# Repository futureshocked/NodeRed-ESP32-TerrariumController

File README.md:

# Node-RED and ESP32: make a terrarium controller

Flows, ESP32 sketches and the KiCad project for the Tech Explorations course [Node-RED and ESP32: make a terrarium controller](https://app.techexplorations.com/courses/node-red-esp32-make-a-terrarium-controller/).

## Project status (October 2026)

The course was recorded in 2020 with Node-RED 1.1 and Node.js 12. The project still works on current software: flow v6 was tested unchanged on Node-RED 5.0.8 with Node.js 22 and 26. The Node-RED editor, the install process and some third-party services have changed since recording.

- **Following the course now?** Read [UPDATE-2026.md](UPDATE-2026.md) first. It covers installing Node-RED 5, the new editor, the deprecated dashboard, Mosquitto 2, and services that have changed (IFTTT webhooks now need a paid plan).
- **What comes next:** [COURSE-UPDATE-PLAN.md](COURSE-UPDATE-PLAN.md) describes the planned revision, including replacing the DHT22, Google Sheets and IFTTT with open-source alternatives.

## What the project does

An ESP32 in the terrarium reads soil moisture, air temperature and humidity, and the voltages of the pump motor supply and its own battery. It publishes these readings over MQTT to a Mosquitto broker on a Raspberry Pi. Node-RED on the Pi subscribes to the readings, shows them on a web dashboard, decides when the soil is dry enough to run the water pump, and sends the pump command back to the ESP32 over MQTT. Later versions add a dashboard control for the moisture threshold, data logging and a low-battery alert.

## Repository contents

### Terrarium controller flows

Each version builds on the previous one, following the course.

| File | Adds |
|---|---|
| `TerrariumController-Flow-v1.json` | Soil moisture gauge and pump control over MQTT |
| `TerrariumController-Flow-v2.json` | Motor and MCU battery voltage gauges |
| `TerrariumController-Flow-v3.json` | Logging to Google Sheets |
| `TerrariumController-Flow-v4.json` | Dashboard control for the soil moisture threshold |
| `TerrariumController-Flow-v5.json` | Air temperature and humidity gauges |
| `TerrariumController-Flow-v6.json` | Low MCU battery alert through IFTTT |

### ESP32 sketches

`ESP32-TerariumControl-v1` to `v6` are the matching sketches. Each folder has an `esp32_secrets.h` file; fill in your Wi-Fi and MQTT broker details before uploading. The sketches need these libraries: EspMQTTClient, TaskScheduler (from v4) and DHTesp (v6).

### Example flows

Smaller flows used in the early lectures to introduce Node-RED concepts:

- Core nodes: `Inject-Function-flow.json`, `Switch-flow.json`, `Global-Variables-context-examples-flows.json`
- Dashboard widgets: `Basic-dashboard-example-flow.json`, `Dashboard-example-flow.json`, `Button-flow.json`, `Dropdown-template-flow.json`, `Form-flow.json`, `gauge-flow.json`
- Messaging and web services: `mqtt-example-flows.json`, `websockets-flow.json`, `dweetio-flow.json`, `ifttt-flow.json`
- DHT22 sensor on the Raspberry Pi: `DHT22-ex1-flow.json`, `DHT22-ex2-flow.json`, `DHT22-complete-example-flow.json`

### Hardware

`KiCad Terrarium Controller project/` contains the schematic and PCB for the controller board (KiCad 9 format), a PDF of the original schematic, and Gerber files. The LED orientation in the schematic was corrected in November 2025.

## Requirements

- Raspberry Pi 3, 4 or 5 with a 64-bit OS (or any computer that runs Node-RED)
- Node-RED 5 on Node.js 24 LTS (Node.js 22.9 or later is required; 26 also works)
- Mosquitto MQTT broker
- `node-red-dashboard` installed from the Node-RED Palette Manager
- ESP32 development board and the components listed in the course

## Importing a flow

In the Node-RED editor, open the main menu, choose Import, and paste the contents of a flow file or select the file. Install `node-red-dashboard` first, otherwise the dashboard nodes appear as "unknown". After importing, open the MQTT broker node and set your broker address, username and password.

## Help

Questions about the course go in the course Q&A. When reporting a problem, include the lecture number, your Node-RED and Node.js versions, and the exact error message.

## Licence

MIT, see [LICENSE](LICENSE).

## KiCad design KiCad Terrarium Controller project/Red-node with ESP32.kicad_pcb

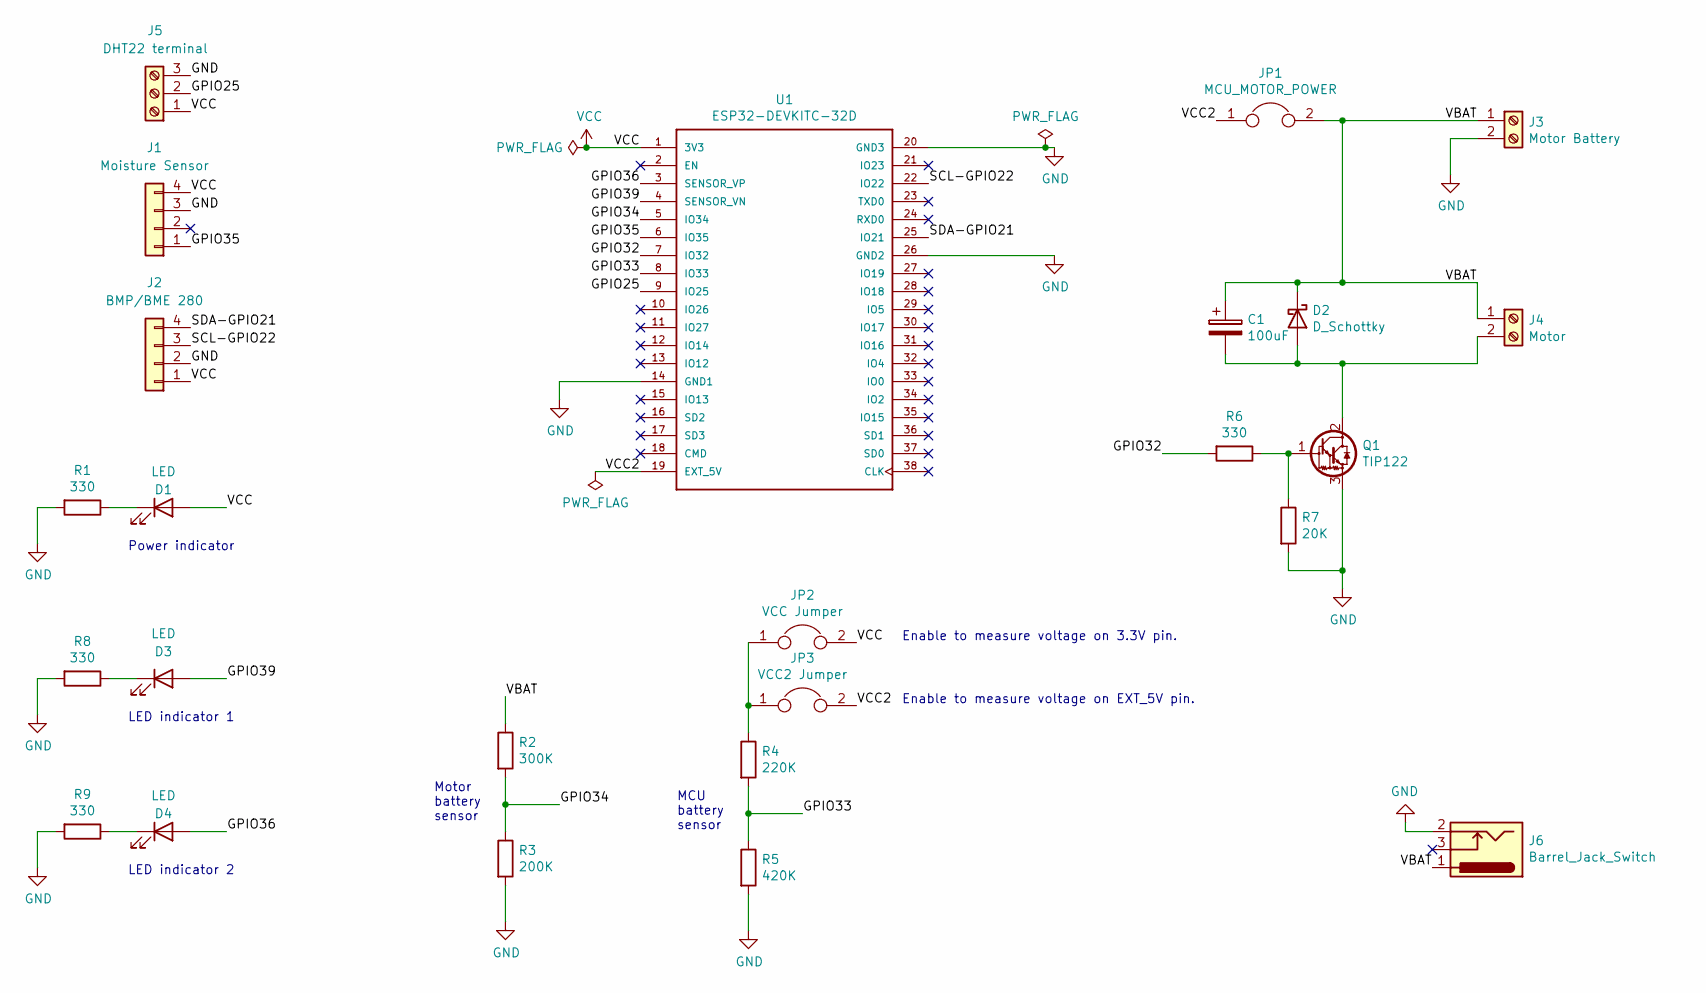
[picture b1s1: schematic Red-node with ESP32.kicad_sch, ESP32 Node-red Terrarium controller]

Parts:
C1: 100uF; CP_Radial_D8.0mm_P3.80mm
D1, D3, D4: LED; LED_D5.0mm
D2: D_Schottky; D_DO-41_SOD81_P7.62mm_Horizontal
J1: Moisture Sensor; PinHeader_1x04_P2.54mm_Vertical
J2: BMP/BME 280; PinHeader_1x04_P2.54mm_Vertical
J3: Motor Battery; TerminalBlock_bornier-2_P5.08mm
J4: Motor; TerminalBlock_bornier-2_P5.08mm
J5: DHT22 terminal; TerminalBlock_bornier-3_P5.08mm
J6: Barrel_Jack_Switch; BarrelJack_Horizontal
JP1: MCU_MOTOR_POWER; PinHeader_1x02_P2.54mm_Vertical
JP2: VCC Jumper; PinHeader_1x02_P2.54mm_Vertical
JP3: VCC2 Jumper; PinHeader_1x02_P2.54mm_Vertical
Q1: TIP122; TO-220-3_Vertical
R1, R6, R8, R9: 330; R_Axial_DIN0207_L6.3mm_D2.5mm_P7.62mm_Horizontal
R2: 300K; R_Axial_DIN0207_L6.3mm_D2.5mm_P7.62mm_Horizontal
R3: 200K; R_Axial_DIN0207_L6.3mm_D2.5mm_P7.62mm_Horizontal
R4: 220K; R_Axial_DIN0207_L6.3mm_D2.5mm_P7.62mm_Horizontal
R5: 420K; R_Axial_DIN0207_L6.3mm_D2.5mm_P7.62mm_Horizontal
R7: 20K; R_Axial_DIN0207_L6.3mm_D2.5mm_P7.62mm_Horizontal
U1: ESP32-DEVKITC-32D; MODULE_ESP32-DEVKITC_PD

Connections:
/GPIO25: J5.2, U1.9 (IO25)
/GPIO32: R6.2, U1.7 (IO32)
/GPIO33: R4.2, R5.1, U1.8 (IO33)
/GPIO34: R2.2, R3.1, U1.5 (IO34)
/GPIO35: J1.1, U1.6 (IO35)
/GPIO36: D4.2 (A), U1.3 (SENSOR_VP)
/GPIO39: D3.2 (A), U1.4 (SENSOR_VN)
/SCL-GPIO22: J2.3, U1.22 (IO22)
/SDA-GPIO21: J2.4, U1.25 (IO21)
/VBAT: C1.1, D2.1 (K), J3.1, J4.1, J6.1, JP1.2, R2.1
/VCC2: JP1.1, JP3.2, U1.19 (EXT_5V)
GND: J1.3, J2.2, J3.2, J5.3, J6.2, Q1.3 (E), R1.2, R3.2, R5.2, R7.2, R8.2, R9.2, U1.14 (GND1), U1.20 (GND3), U1.26 (GND2)
unnamed: D1.1 (K), R1.1
unnamed: C1.2, D2.2 (A), J4.2, Q1.2 (C)
unnamed: D3.1 (K), R8.1
unnamed: D4.1 (K), R9.1
unnamed: JP2.1, JP3.1, R4.1
unnamed: Q1.1 (B), R6.1, R7.1
VCC: D1.2 (A), J1.4, J2.1, J5.1, JP2.2, U1.1 (3V3)

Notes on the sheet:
LED indicator 2
Power indicator
Enable to measure voltage on EXT_5V pin.
Enable to measure voltage on 3.3V pin.
Motor battery sensor
LED indicator 1
MCU battery sensor

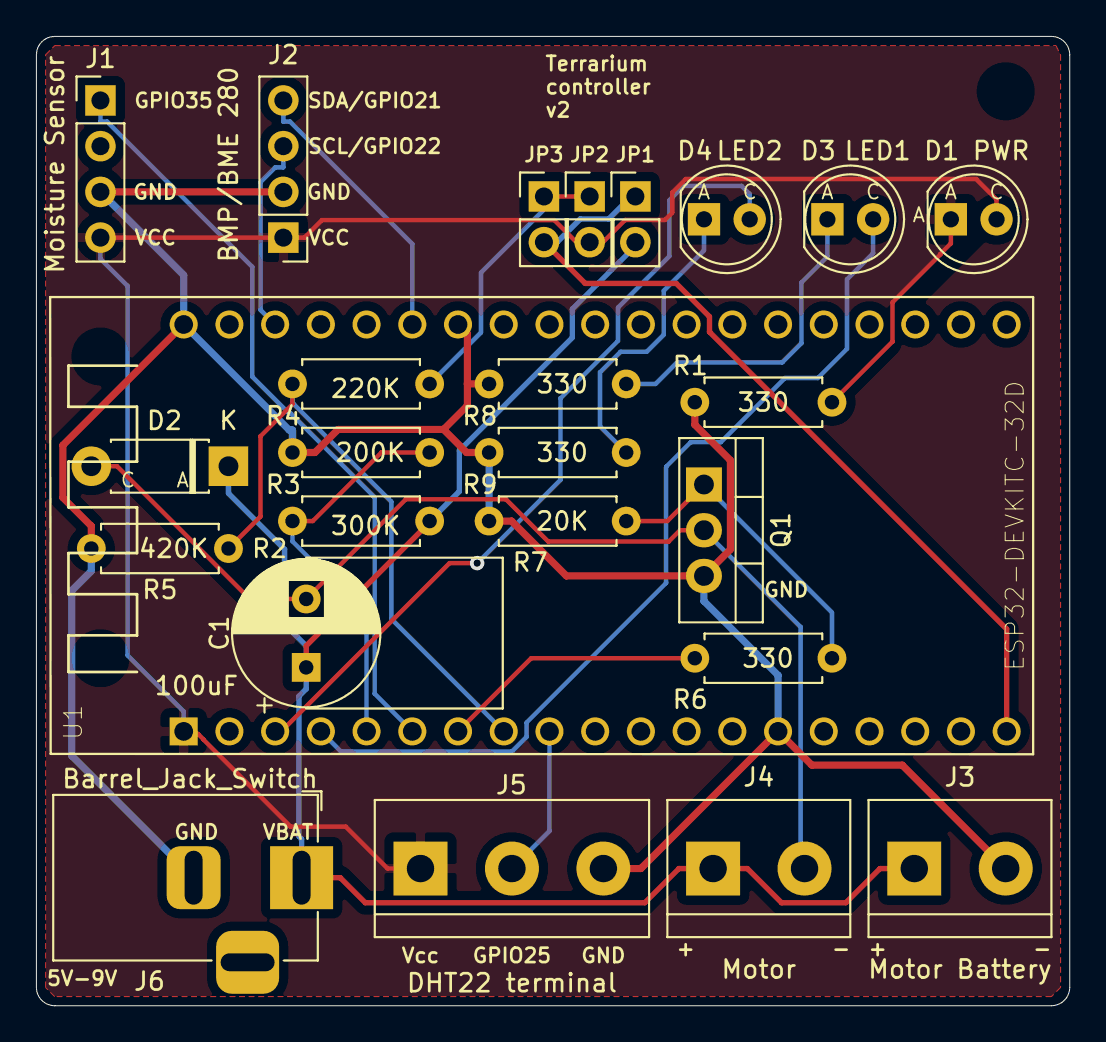
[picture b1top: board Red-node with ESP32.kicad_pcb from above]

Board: 2 copper layers, 57.4 x 53.8 mm, 25 parts (0 on the bottom side), 19 nets.

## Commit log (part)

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2020-07-24 New simple flow examples.
2020-08-25 Added new header
2025-11-26 Fixed incorrect LED orientation in the schematic
2025-11-27 Fixed issues with LED
    Both schematic and layouts are fixed.
